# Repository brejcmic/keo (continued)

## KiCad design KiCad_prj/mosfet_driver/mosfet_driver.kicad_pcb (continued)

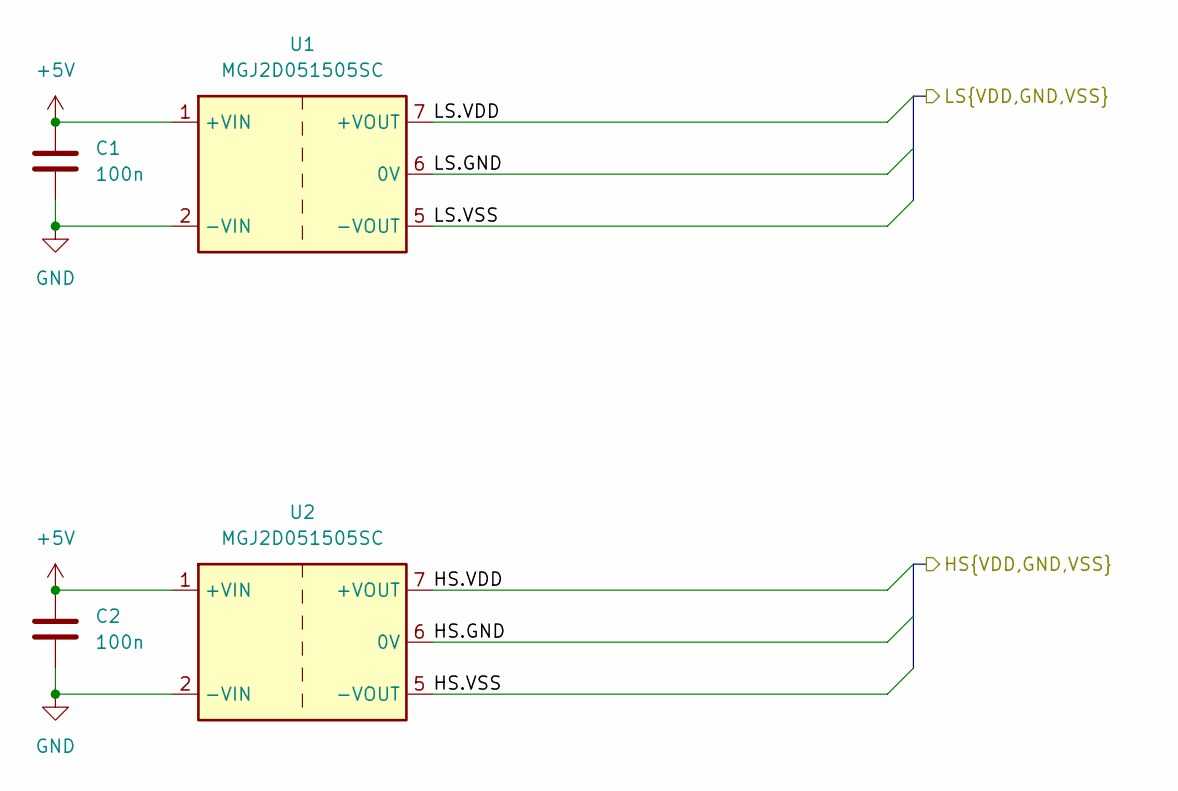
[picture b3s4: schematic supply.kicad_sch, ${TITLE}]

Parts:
C1, C2: 100n; C_0805_2012Metric; JLCPCB Part # C28233
U1, U2: MGJ2D051505SC; Converter_DCDC_Murata_MGJ2DxxxxxxSC_THT

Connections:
+5V: C1.2, C2.2, U1.1 (+VIN), U2.1 (+VIN); also elsewhere on the board
/Driver/HS.GND: U2.6 (0V); also elsewhere on the board
/Driver/HS.VDD: U2.7 (+VOUT); also elsewhere on the board
/Driver/HS.VSS: U2.5 (-VOUT); also elsewhere on the board
/Driver/LS.GND: U1.6 (0V); also elsewhere on the board
/Driver/LS.VDD: U1.7 (+VOUT); also elsewhere on the board
/Driver/LS.VSS: U1.5 (-VOUT); also elsewhere on the board
GND: C1.1, C2.1, U1.2 (-VIN), U2.2 (-VIN); also elsewhere on the board

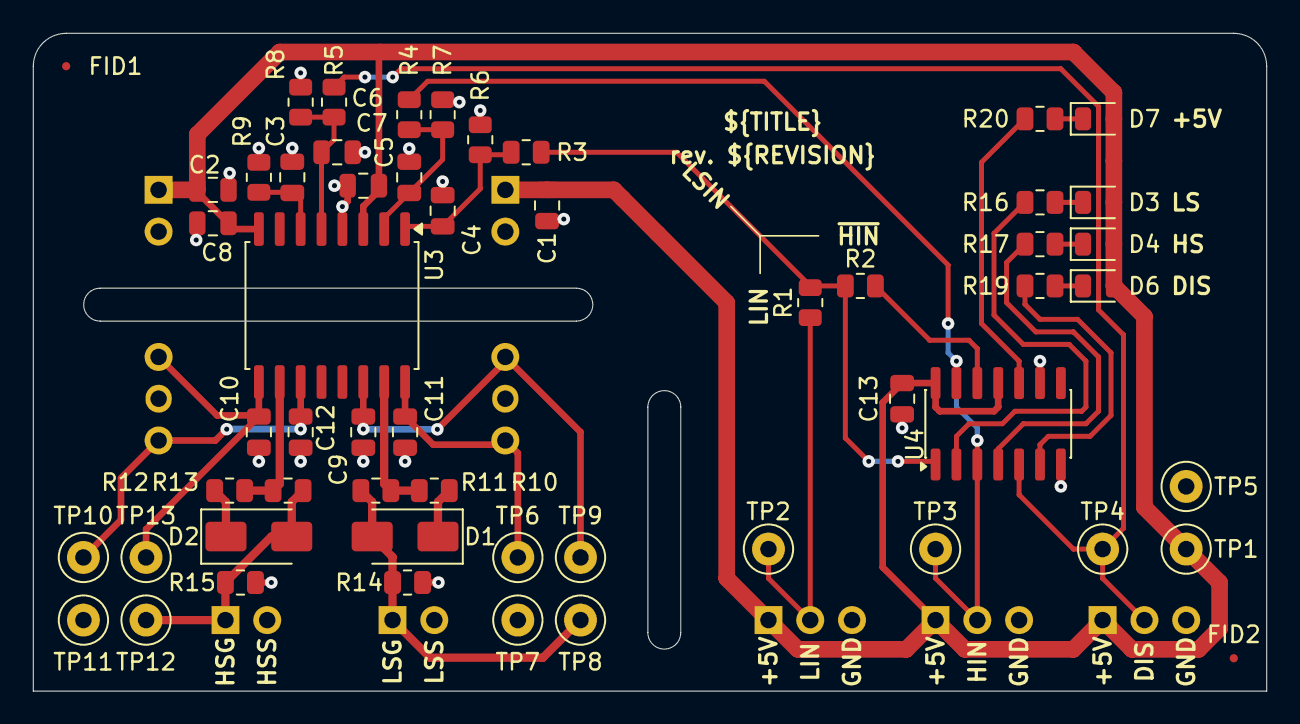
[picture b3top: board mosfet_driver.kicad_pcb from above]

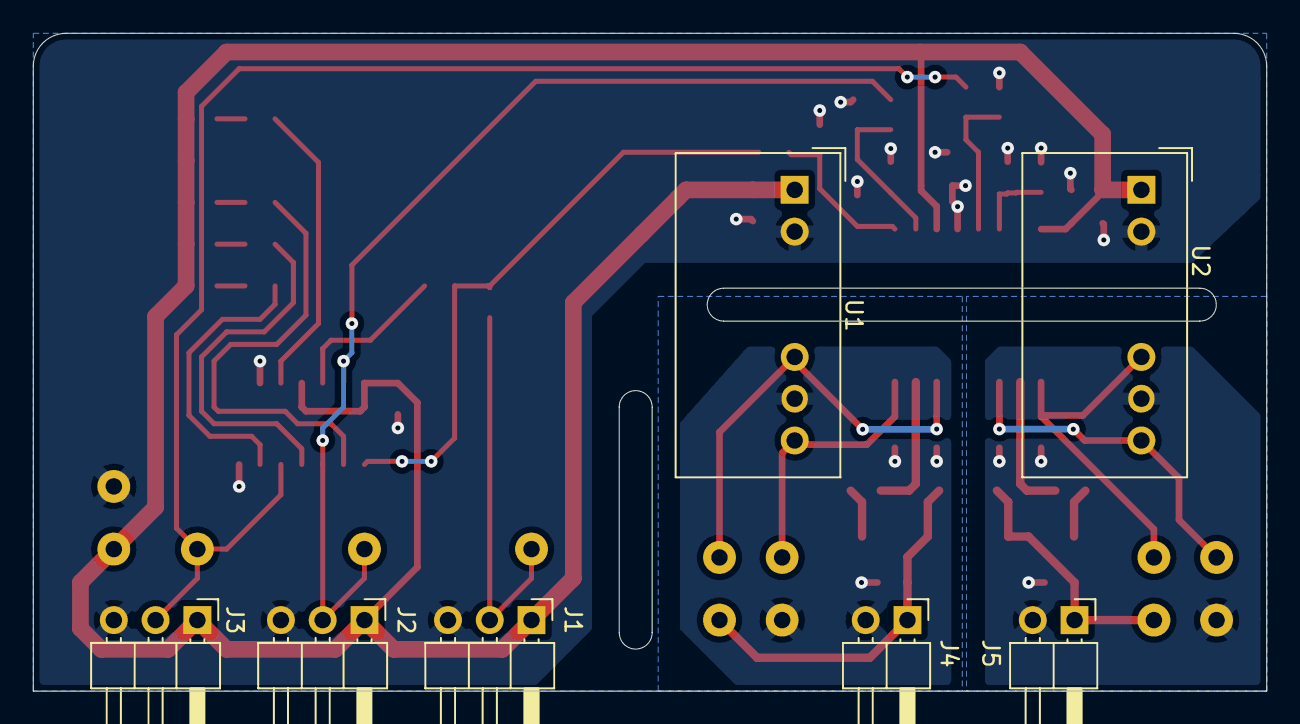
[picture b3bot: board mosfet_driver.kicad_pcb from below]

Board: 2 copper layers, 75.0 x 40.0 mm, 62 parts (7 on the bottom side), 31 nets.

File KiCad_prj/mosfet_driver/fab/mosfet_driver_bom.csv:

"Comment","Designator","Footprint","JLCPCB Part #"
"100n","C1,C2,C13","Capacitor_SMD:C_0805_2012Metric","C28233"
"470p","C3","Capacitor_SMD:C_0805_2012Metric","C1743"
"22p","C4,C5,C6","Capacitor_SMD:C_0805_2012Metric","C1804"
"1u","C7,C8,C9,C10,C11,C12","Capacitor_SMD:C_0805_2012Metric","C28323"
"SS14","D1,D2","Diode_SMD:D_SMA","C2480"
"RED","D3,D4,D5,D6,D7","LED_SMD:LED_0805_2012Metric","C84256"
"0R","R1,R2","Resistor_SMD:R_0805_2012Metric","C17477"
"100R","R3,R4,R5","Resistor_SMD:R_0805_2012Metric","C17408"
"10k","R6,R7,R8,R14,R15","Resistor_SMD:R_0805_2012Metric","C17414"
"47k","R9","Resistor_SMD:R_0805_2012Metric","C17713"
"3R3","R10,R12","Resistor_SMD:R_0805_2012Metric","C16257"
"10R","R11,R13","Resistor_SMD:R_0805_2012Metric","C17415"
"1k","R16,R17,R18,R19,R20","Resistor_SMD:R_0805_2012Metric","C17513"
"UCC21520ADW","U3","Package_SO:SOIC-16W_7.5x10.3mm_P1.27mm","C2863027"
"74HC14","U4","Package_SO:SOIC-14_3.9x8.7mm_P1.27mm","C5605"

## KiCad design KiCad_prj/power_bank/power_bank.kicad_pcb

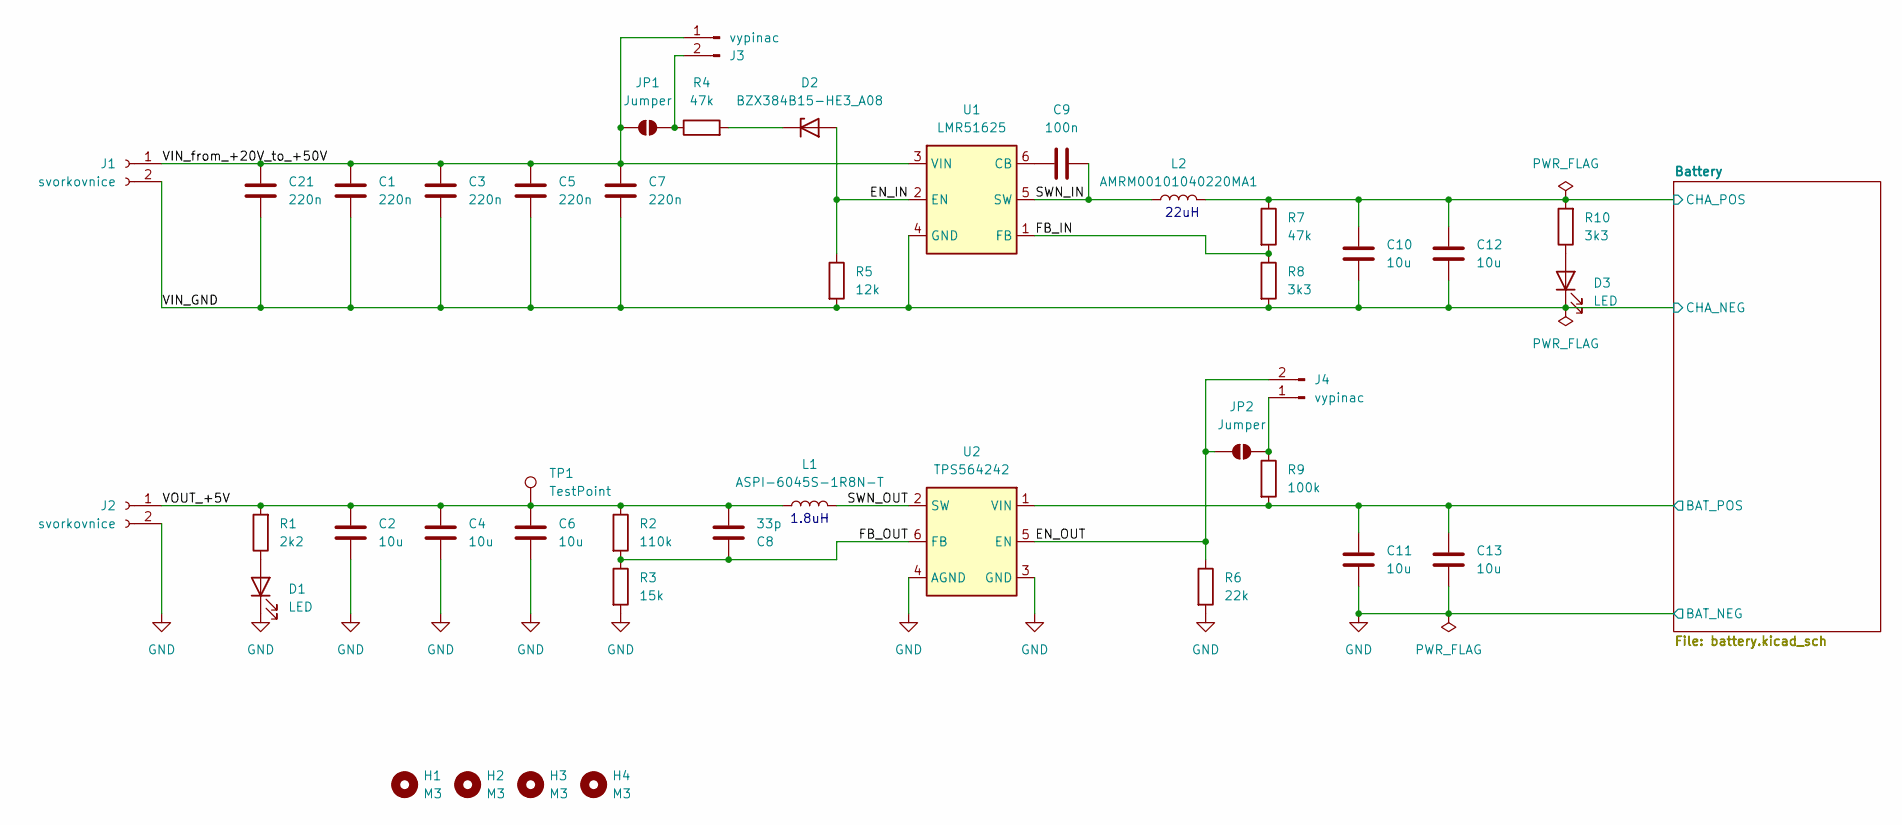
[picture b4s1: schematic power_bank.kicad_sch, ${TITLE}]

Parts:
C1, C3, C5, C7, C21: 220n; C_0805_2012Metric; JLCPCB Part # C6119933
C2, C4, C6, C10, C11, C12, C13: 10u; C_0805_2012Metric; JLCPCB Part # C15850
C8: 33p; C_0805_2012Metric; JLCPCB Part # C107115
C9: 100n; C_0805_2012Metric; JLCPCB Part # C28233
D1, D3: LED; LED_D3.0mm
D2: BZX384B15-HE3_A08; D_SOD-323F; JLCPCB Part # C49296788
H1, H2, H3, H4: M3; MountingHole_3.2mm_M3
J1, J2: svorkovnice; PhoenixContact_MSTBVA_2,5_2-G-5,08_1x02_P5.08mm_Vertical
J3, J4: vypinac; PinHeader_1x02_P2.54mm_Vertical
JP1, JP2: Jumper; SolderJumper-2_P1.3mm_Open_RoundedPad1.0x1.5mm
L1: ASPI-6045S-1R8N-T; L_APV_ANR6045; JLCPCB Part # C2997654
L2: AMRM00101040220MA1; L_10.4x10.4_H4.8; JLCPCB Part # C10165
R1: 2k2; R_0805_2012Metric; JLCPCB Part # C17520
R2: 110k; R_0805_2012Metric; JLCPCB Part # C17422
R3: 15k; R_0805_2012Metric; JLCPCB Part # C17475
R4, R7: 47k; R_0805_2012Metric; JLCPCB Part # C17713
R5: 12k; R_0805_2012Metric; JLCPCB Part # C17444
R6: 22k; R_0805_2012Metric; JLCPCB Part # C17560
R8, R10: 3k3; R_0805_2012Metric; JLCPCB Part # C26010
R9: 100k; R_0805_2012Metric; JLCPCB Part # C149504
TP1: TestPoint; TestPoint_Pad_D2.0mm
U1: LMR51625; SOT-23-6; JLCPCB Part # C45262767
U2: TPS564242; SOT-563; JLCPCB Part # C5219267

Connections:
/Battery/BAT_POS: C11.1, C13.1, R9.2, U2.1 (VIN); also elsewhere on the board
/Battery/CHA_POS: C10.1, C12.1, L2.2, R7.1, R10.2; also elsewhere on the board
/EN_IN: D2.2 (A), R5.1, U1.2 (EN)
/EN_OUT: J4.2, JP2.1 (A), R6.1, U2.5 (EN)
/FB_IN: R7.2, R8.1, U1.1 (FB)
/FB_OUT: C8.2, R2.2, R3.1, U2.6 (FB)
/SWN_IN: C9.2, L2.1, U1.5 (SW)
/SWN_OUT: L1.2, U2.2 (SW)
/VIN_GND: C1.2, C3.2, C5.2, C7.2, C10.2, C12.2, C21.2, D3.1 (K), J1.2, R5.2, R8.2, U1.4 (GND); also elsewhere on the board
/VIN_from_+20V_to_+50V: C1.1, C3.1, C5.1, C7.1, C21.1, J1.1, J3.1, JP1.1 (A), U1.3 (VIN)
/VOUT_+5V: C2.1, C4.1, C6.1, C8.1, J2.1, L1.1, R1.2, R2.1, TP1.1
GND: C2.2, C4.2, C6.2, C11.2, C13.2, D1.1 (K), J2.2, R3.2, R6.2, U2.3 (GND), U2.4 (AGND); also elsewhere on the board
unnamed: D1.2 (A), R1.1
unnamed: D2.1 (K), R4.2
unnamed: D3.2 (A), R10.1
unnamed: J3.2, JP1.2 (B), R4.1
unnamed: J4.1, JP2.2 (B), R9.1
unnamed: C9.1, U1.6 (CB)

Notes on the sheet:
1.8uH
22uH

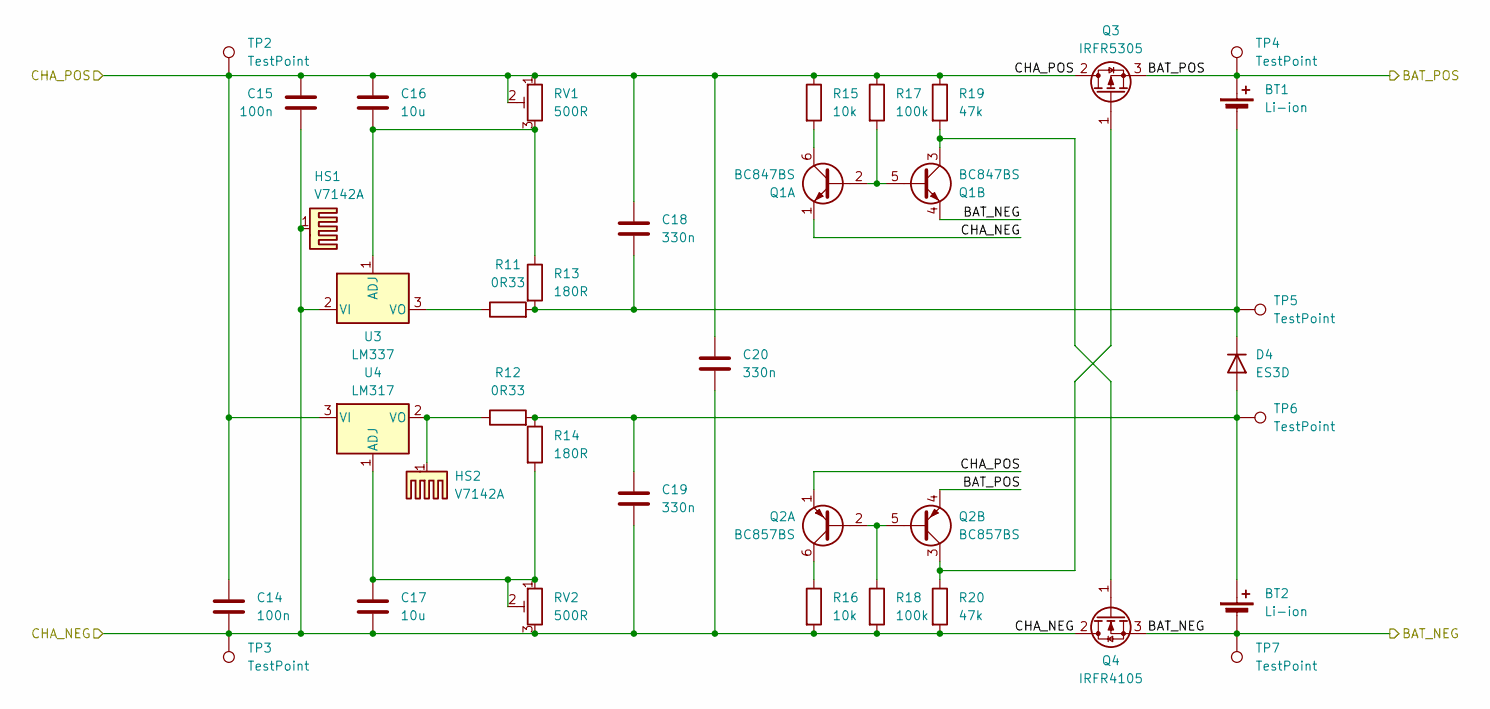
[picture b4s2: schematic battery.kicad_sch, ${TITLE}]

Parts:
BT1, BT2: Li-ion; BatteryHolder_MPD_BH-18650-PC
C14, C15: 100n; C_0805_2012Metric; JLCPCB Part # C28233
C16, C17: 10u; C_0805_2012Metric; JLCPCB Part # C15850
C18, C19, C20: 330n; C_0805_2012Metric; JLCPCB Part # C1740
D4: ES3D; D_SMC; JLCPCB Part # C16235
HS1, HS2: V7142A
Q1: BC847BS; SOT-363_SC-70-6; JLCPCB Part # C8653
Q2: BC857BS; SOT-363_SC-70-6; JLCPCB Part # C8654
Q3: IRFR5305; TO-252-2; JLCPCB Part # C2624
Q4: IRFR4105; TO-252-2; JLCPCB Part # C22366766
R11, R12: 0R33; R_Axial_DIN0411_L9.9mm_D3.6mm_P12.70mm_Horizontal
R13, R14: 180R; R_0805_2012Metric; JLCPCB Part # C1339
R15, R16: 10k; R_0805_2012Metric; JLCPCB Part # C17414
R17, R18: 100k; R_0805_2012Metric; JLCPCB Part # C149504
R19, R20: 47k; R_0805_2012Metric; JLCPCB Part # C17713
RV1, RV2: 500R; Potentiometer_ACP_CA9-V10_Vertical
TP2, TP3, TP4, TP5, TP6, TP7: TestPoint; TestPoint_Pad_D2.0mm
U3: LM337; TO-220-3_Vertical
U4: LM317; TO-220-3_Vertical

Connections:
/Battery/BAT_POS: BT1.1 (+), Q2.4 (E2), Q3.3 (S), TP4.1; also elsewhere on the board
/Battery/CHA_POS: C14.1, C15.1, C16.1, C18.1, C20.1, Q2.1 (E1), Q3.2 (D), R15.1, R17.1, R19.1, RV1.1, RV1.2, TP2.1, U4.3 (VI); also elsewhere on the board
/VIN_GND: C14.2, C15.2, C17.2, C19.2, C20.2, HS1.1, Q1.1 (E1), Q4.2 (D), R16.2, R18.2, R20.2, RV2.3, TP3.1, U3.2 (VI); also elsewhere on the board
GND: BT2.2 (-), Q1.4 (E2), Q4.3 (S), TP7.1; also elsewhere on the board
unnamed: BT1.2 (-), C18.2, D4.1 (K), R11.2, R13.2, TP5.1
unnamed: BT2.1 (+), C19.1, D4.2 (A), R12.2, R14.1, TP6.1
unnamed: Q1.2 (B1), Q1.5 (B2), R17.2
unnamed: Q1.6 (C1), R15.2
unnamed: Q1.3 (C2), Q4.1 (G), R19.2
unnamed: Q2.2 (B1), Q2.5 (B2), R18.1
unnamed: Q2.6 (C1), R16.1
unnamed: Q2.3 (C2), Q3.1 (G), R20.1
unnamed: C16.2, R13.1, RV1.3, U3.1 (ADJ)
unnamed: R11.1, U3.3 (VO)
unnamed: C17.1, R14.2, RV2.1, RV2.2, U4.1 (ADJ)
unnamed: HS2.1, R12.1, U4.2 (VO)

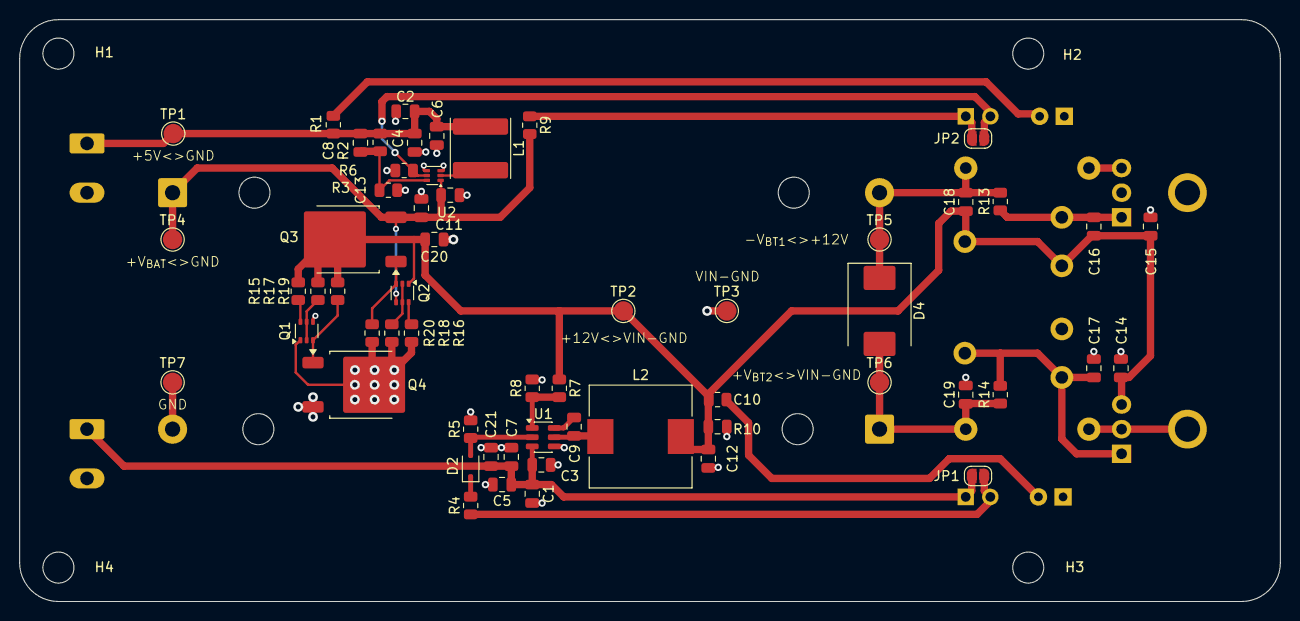
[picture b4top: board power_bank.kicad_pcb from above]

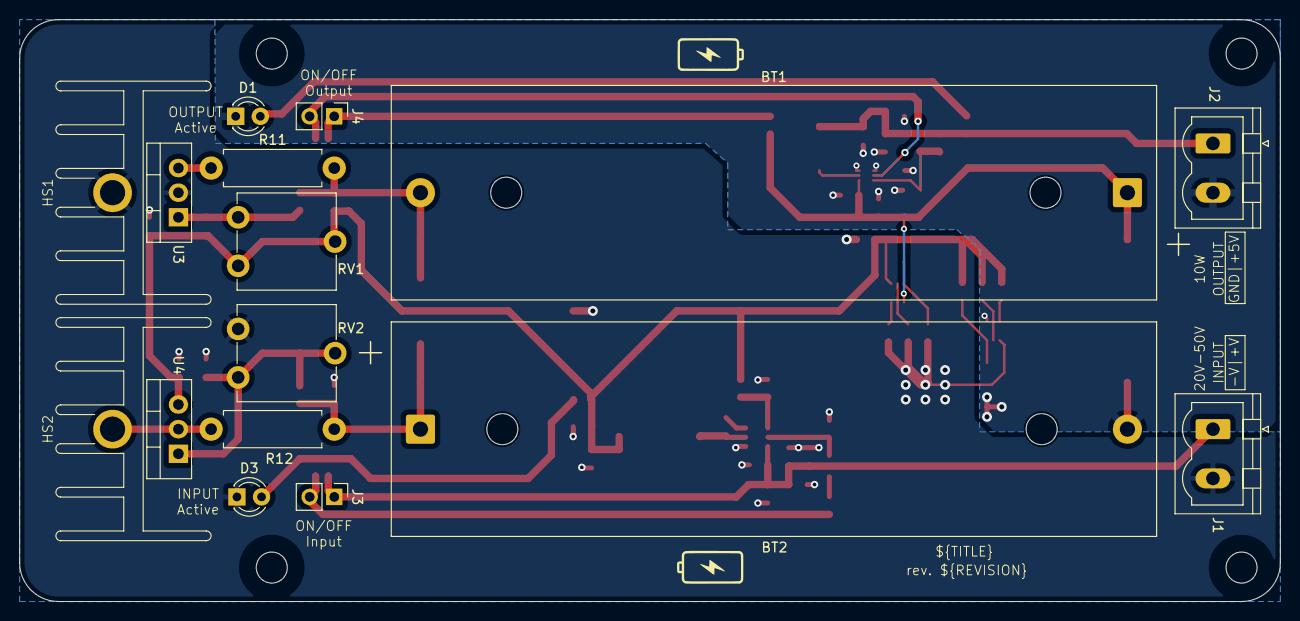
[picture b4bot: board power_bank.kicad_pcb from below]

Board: 2 copper layers, 130.0 x 60.0 mm, 78 parts (16 on the bottom side), 30 nets.

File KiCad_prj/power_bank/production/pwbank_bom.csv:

"Reference","Value","Footprint","JLCPCB Part #"
"C1,C3,C5,C7,C21","220n","Capacitor_SMD:C_0805_2012Metric","C6119933"
"C2,C4,C6,C10,C11,C12,C13,C16,C17","10u","Capacitor_SMD:C_0805_2012Metric","C15850"
"C8","33p","Capacitor_SMD:C_0805_2012Metric","C107115"
"C9,C14,C15","100n","Capacitor_SMD:C_0805_2012Metric","C28233"
"C18,C19,C20","330n","Capacitor_SMD:C_0805_2012Metric","C1740"
"D2","BZX384B15-HE3_A08","Diode_SMD:D_SOD-323F","C49296788"
"D4","ES3D","Diode_SMD:D_SMC","C16235"
"L1","ASPI-6045S-1R8N-T","Inductor_SMD:L_APV_ANR6045","C2997654"
"L2","AMRM00101040220MA1","Inductor_SMD:L_10.4x10.4_H4.8","C10165"
"Q1","BC847BS","Package_TO_SOT_SMD:SOT-363_SC-70-6","C8653"
"Q2","BC857BS","Package_TO_SOT_SMD:SOT-363_SC-70-6","C8654"
"Q3","IRFR5305","Package_TO_SOT_SMD:TO-252-2","C2624"
"Q4","IRFR4105","Package_TO_SOT_SMD:TO-252-2","C22366766"
"R1","2k2","Resistor_SMD:R_0805_2012Metric","C17520"
"R2","110k","Resistor_SMD:R_0805_2012Metric","C4310"
"R3","15k","Resistor_SMD:R_0805_2012Metric","C17475"
"R4,R7,R19,R20","47k","Resistor_SMD:R_0805_2012Metric","C17713"
"R5","12k","Resistor_SMD:R_0805_2012Metric","C17444"
"R6","22k","Resistor_SMD:R_0805_2012Metric","C17560"
"R8,R10","3k3","Resistor_SMD:R_0805_2012Metric","C26010"
"R9,R17,R18","100k","Resistor_SMD:R_0805_2012Metric","C149504"
"R13,R14","180R","Resistor_SMD:R_0805_2012Metric","C1339"
"R15,R16","10k","Resistor_SMD:R_0805_2012Metric","C17414"
"U1","LMR51625","Package_TO_SOT_SMD:SOT-23-6","C45262767"
"U2","TPS564242","Package_TO_SOT_SMD:SOT-563","C5219267"

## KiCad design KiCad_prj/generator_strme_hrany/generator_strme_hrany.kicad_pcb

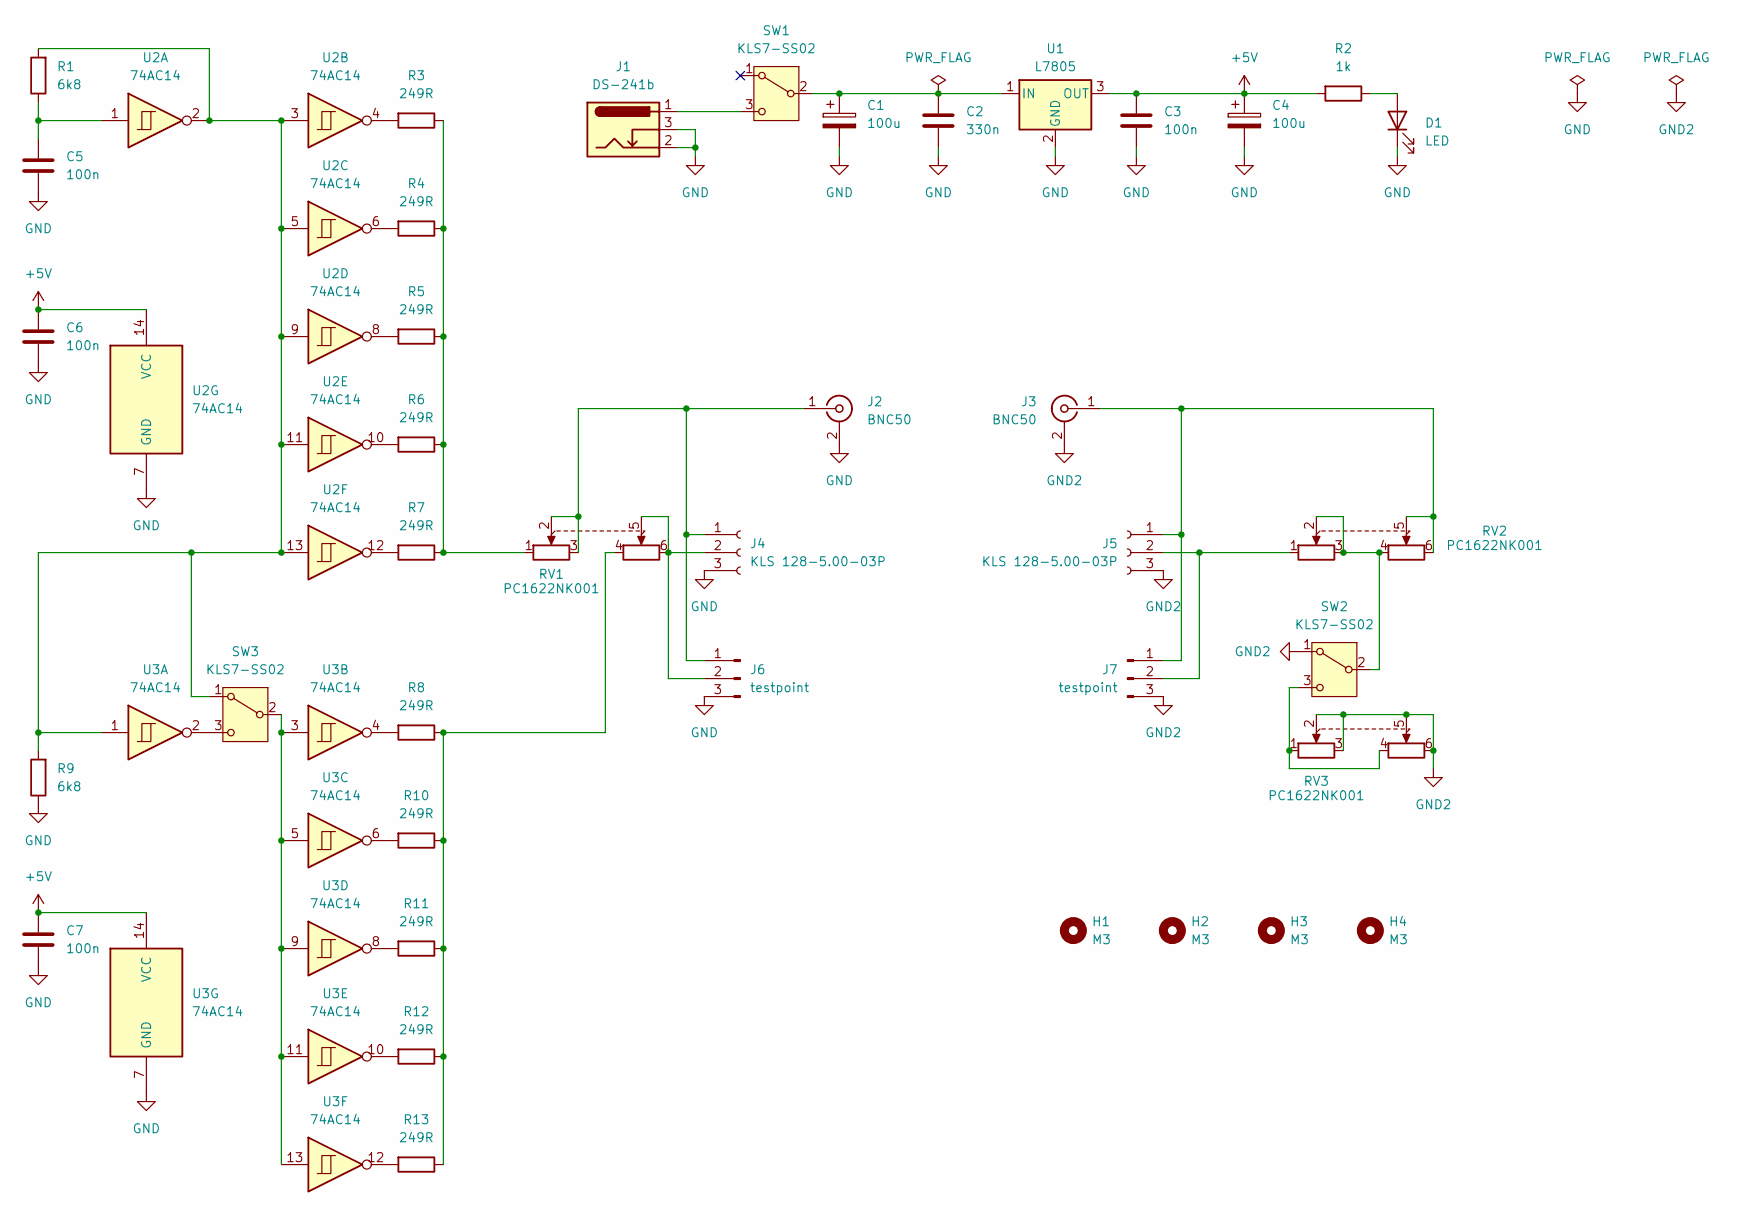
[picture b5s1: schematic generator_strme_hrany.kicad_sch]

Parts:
C1, C4: 100u; CP_Radial_D6.3mm_P2.50mm
C2: 330n; C_Rect_L7.0mm_W2.5mm_P5.00mm
C3, C5, C6, C7: 100n; C_Rect_L7.0mm_W2.5mm_P5.00mm
D1: LED; LED_D3.0mm
H1, H2, H3, H4: M3; MountingHole_3.2mm_M3
J1: DS-241b; BarrelJack_GCT_DCJ200-10-A_Horizontal
J2, J3: BNC50; BNC_Amphenol_B6252HB-NPP3G-50_Horizontal
J4, J5: KLS 128-5.00-03P; JST_NV_B03P-NV_1x03_P5.00mm_Vertical
J6, J7: testpoint; SolderWire-1sqmm_1x03_P5.4mm_D1.4mm_OD2.7mm
R1, R9: 6k8; R_Axial_DIN0207_L6.3mm_D2.5mm_P7.62mm_Horizontal
R2: 1k; R_Axial_DIN0207_L6.3mm_D2.5mm_P7.62mm_Horizontal
R3, R4, R5, R6, R7, R8, R10, R11, R12, R13: 249R; R_Axial_DIN0207_L6.3mm_D2.5mm_P7.62mm_Horizontal
RV1, RV2, RV3: PC1622NK001; Potentiometer_Alps_RK163_Dual_Horizontal
SW1, SW2, SW3: KLS7-SS02; KLS7-SS02-12F20
U1: L7805; TO-220-3_Horizontal_TabDown
U2, U3: 74AC14; CERDIP-14_W7.62mm_SideBrazed_LongPads

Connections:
+5V: C3.1, C4.1, C6.1, C7.1, R2.2, U1.3 (OUT), U2.14 (VCC), U3.14 (VCC)
GND: C1.2, C2.2, C3.2, C4.2, C5.2, C6.2, C7.2, D1.1 (K), J1.2, J1.3, J2.2 (Ext), J4.3, J6.3, R9.1, U1.2 (GND), U2.7 (GND), U3.7 (GND)
GND2: J3.2 (Ext), J5.3, J7.3, RV3.2, RV3.3, RV3.5, RV3.6, SW2.1 (A)
unnamed: C5.1, R1.1, U2.1
unnamed: D1.2 (A), R2.1
unnamed: J2.1 (In), J4.1, J6.1, RV1.2, RV1.3
unnamed: J3.1 (In), J5.1, J7.1, RV2.5, RV2.6
unnamed: J4.2, J6.2, RV1.5, RV1.6
unnamed: J5.2, J7.2, RV2.1
unnamed: R3.1, R4.1, R5.1, R6.1, R7.1, RV1.1
unnamed: R3.2, U2.4
unnamed: R4.2, U2.6
unnamed: R5.2, U2.8
unnamed: R6.2, U2.10
unnamed: R7.2, U2.12
unnamed: R8.2, U3.4
unnamed: R8.1, R10.1, R11.1, R12.1, R13.1, RV1.4
unnamed: R10.2, U3.6
unnamed: R11.2, U3.8
unnamed: R12.2, U3.10
unnamed: R13.2, U3.12
unnamed: C1.1, C2.1, SW1.2 (B), U1.1 (IN)
unnamed: J1.1, SW1.3 (C)
unnamed: RV2.2, RV2.3, RV2.4, SW2.2 (B)
unnamed: RV3.1, RV3.4, SW2.3 (C)
unnamed: R1.2, R9.2, SW3.1 (A), U2.2, U2.3, U2.5, U2.9, U2.11, U2.13, U3.1
unnamed: SW3.2 (B), U3.3, U3.5, U3.9, U3.11, U3.13
unnamed: SW3.3 (C), U3.2

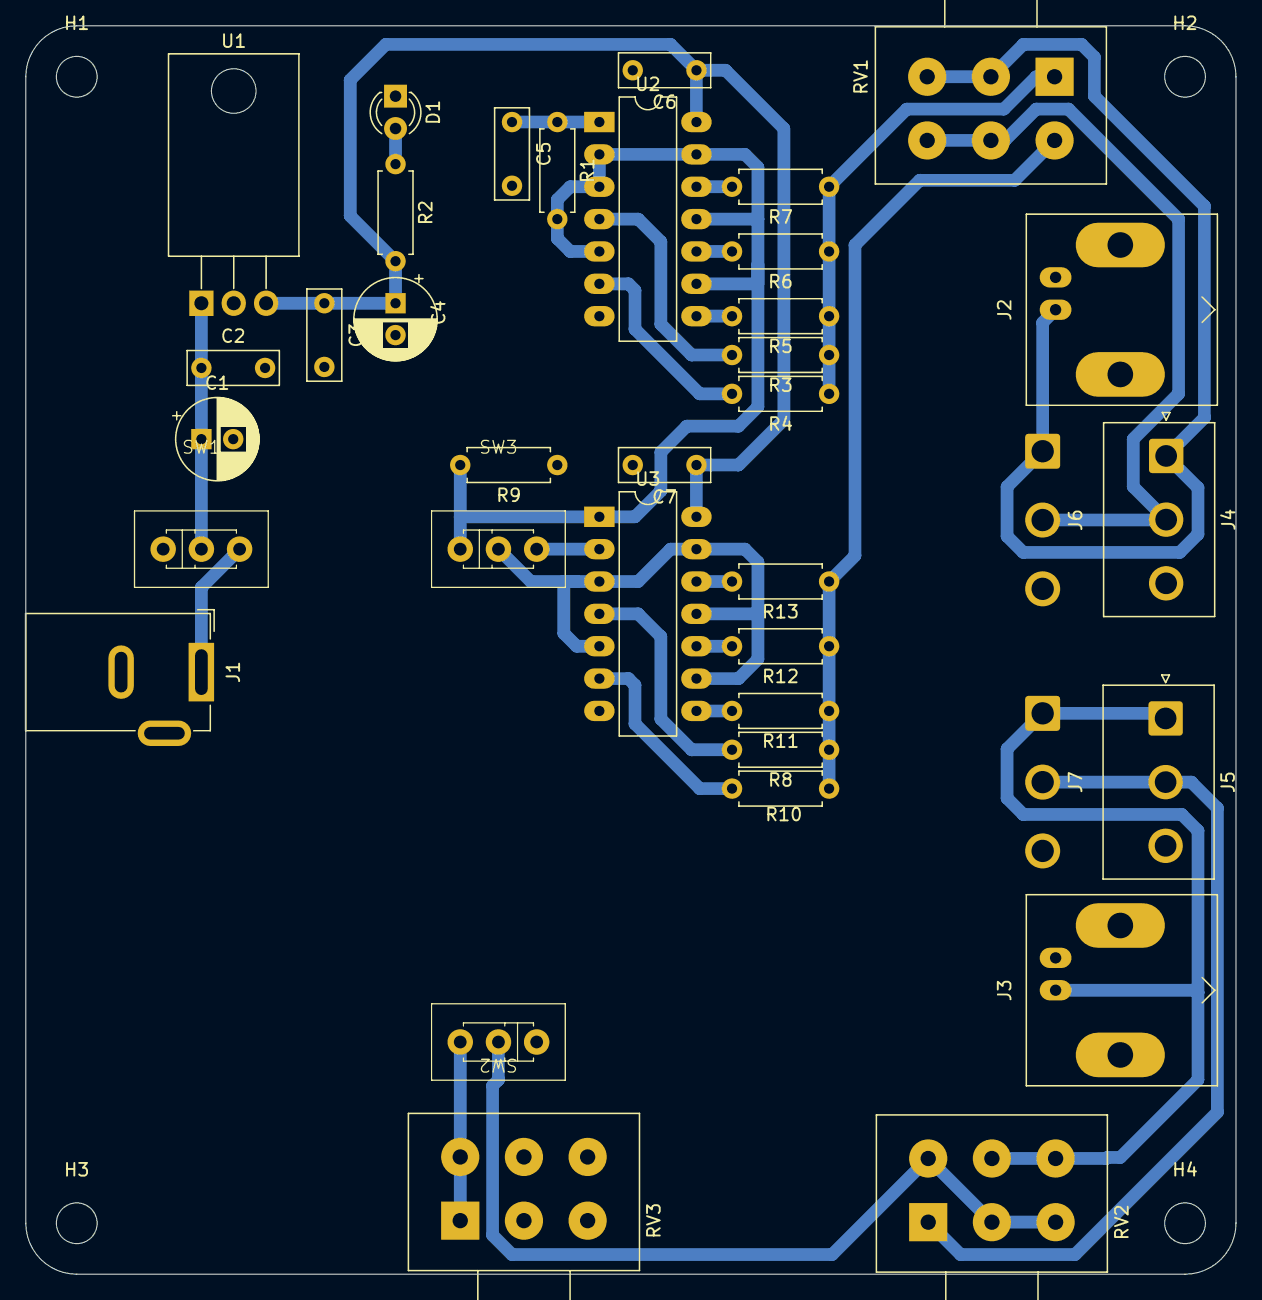
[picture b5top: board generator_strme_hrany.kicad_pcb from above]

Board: 2 copper layers, 95.0 x 98.0 mm, 41 parts (0 on the bottom side), 28 nets.

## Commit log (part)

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2021-09-20 Pocatecni verze prezentaci
2021-09-20 Oprava uvodni prezentace dle pozadavku 2021. Pridany ukazky praci studentu
2021-09-20 Změna ukazek praci studentu za tz, ktere lepe respektuji cile predmetu.
2021-10-05 Pripravena prezentace cviceni 3
2021-10-05 Upravena prezentace cviceni 2
2021-10-05 Uprava obrazku
2021-10-10 P4: novy projekt a knihovny
    Doplneny slajdy pro zalozeni noveho projektu a prirazeni vlastnich knihoven.
2021-10-18 P4: razitko a umistovani soucastek
2021-10-18 P4: temer dokoncene pridavani listu
2021-10-19 P4: dokončeny všechny body
2021-10-19 Pridan ukazkovy projekt
2021-10-19 Doplneni ukazkoveho projektu starym seznamem knihoven.
2022-09-19 Aktualizace roku
2023-10-02 Pridana prednaska 2 pro plosne spoje
2023-10-24 Predelani ukazkoveho projektu na verzi 7.0
2023-10-24 update prezentaci
2024-09-24 pridany obrazky instalace kicad 8.0.5
2024-09-29 Pridany simulace
2024-09-30 Uprava prezentace prototypu
2025-10-05 uprava cv3 2024
2025-10-05 Aktualizace prezentace cviceni cv3
2025-10-20 Simulace sinusoveho tvarovace signalu
2025-10-27 Simulace diferencialniho vedeni
2025-10-28 Navrh generatoru strme hrany
2025-10-30 Mosfet driver projekt
2025-11-02 Doplnen text do schematu a na dps
2025-11-02 Upravena adresarova struktura
2025-11-02 pridan zdroj do simulace crosstalk -> crosstalk_diff
2025-11-09 Mosfet driver v rev. 1.0 odeslan do vyroby
2025-11-10 pridana simulace dopredneho menice
2025-11-11 doplnen popis do simulace lt_spice_forward
2025-11-16 doplnena verze forward converter s kondenzatorem proti zemi
2025-11-19 Dokoncena DPS pripravku strme hrany
2025-11-21 Vyrobni data pro generator strme hrany
2025-11-25 Oprava budice na zaklade vysledku zkousek, pridano drazkovani
2025-11-26 Vytvořen symbol a pouzdro pro mosfet driver
2026-01-14 power_bank: navrh baterioveho obvodu
2026-01-15 power_bank: dokonceny navrh schema
2026-01-15 power_bank: doplnena pouzdra
2026-01-15 pocatek dps
2026-01-16 power_bank: priprava pouzdra chladice
2026-01-16 power_bank: zakladni vzhled DPS
2026-01-17 power_bank: vyrobni rozmisteni prvku, doplnit uzivatelske popisky
2026-01-17 power_bank: dokoncena DPS
2026-01-17 Odeslano do vyroby, rev 1.0
2026-01-28 Doplnen interaktivni BOM
2026-01-29 Oprava objednavaciho kodu u power_bank
